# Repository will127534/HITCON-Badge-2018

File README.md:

# HITCON-Badge-2018
HITCON Badge 2018 files

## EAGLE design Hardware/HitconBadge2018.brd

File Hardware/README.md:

#Hitcon Badge 2018 硬體架構
---

幾個重要的Chip分別如下:
Main System on Chip: MT7697[官方網頁](https://labs.mediatek.com/zh-tw/chipset/MT7697)  
NFC Controller: PN532  
Display: Waveshare 2.13" [官方網頁](https://www.waveshare.com/wiki/2.13inch_e-Paper_HAT)  
Secure Element: SLE97

MT7697的周邊是基於LinkIt 7697[(官方網頁)](https://docs.labs.mediatek.com/resource/mt7687-mt7697/en/get-started-linkit-7697-hdk) 開發版所做的二次開發，所以使用上如同LinkIt 7697

接下來分幾個子系統來說明  

### e-Paper:  

Waveshare 2.13" e-Paper 解析度為250x122的黑白雙色的電子紙且支援區域更新
和MT7697的接線圖如下表:

| E-Paper pin | MT7697 pin | Arduino |
| -------- | -------- | -------- |
| Busy     | GPIO34     | 4     |
| RST     | GPIO33     | 5     |
| D/C     | GPIO36     | 7     |
| /CS     | GPIO32     | 10     |
| SCK     | GPIO31     | 13     |
| MOSI     | GPIO29     | 11     |
  
電子紙的Graphics Library使用的是Adafruit GFX [(Link)](https://learn.adafruit.com/adafruit-gfx-graphics-library/overview)
Adafruit GFX提供了幾個畫圖的操作API，不過要注意的是只有黑白兩色  
而底層的電子紙控制則是用GxEPD Library[(Link)](https://github.com/ZinggJM/GxEPD)
另外就是由於電子紙的全域更新速度較慢，這個型號另外提供了一個區域更新的方法，也就是只更新部分區域的畫面  
但是要注意的是區域更新會有殘影留在螢幕上，所以幾次的區域更新之後需要一次全域更新去清除殘影。全域更新大約需要6s，而區域更新只需要<0.5s  

### NFC:
也是用Adafruit的Library [(Link)](https://github.com/adafruit/Adafruit-PN532)
和MT7697的接線圖如下表:

| PN532 | MT7697 pin | Arduino |
| -------- | -------- | -------- |
| I2C     | I2C     | I2C     |
| RST     | GPIO60     | 17     |
| INT     | GPIO0     | 2     |

### Secure Element:  
待Update
和MT7697的接線圖如下表:

| SLE97 | MT7697 pin | Arduino |
| -------- | -------- | -------- |
| SPI     | SPI     | SPI     |
| CS     | GPIO39     | 3     |

### Button Array:  
由於MT7697 IO不夠用了，所以矩陣鍵盤使用的是類比的方式，
藉由按鈕按下後所產生的不同組合的電阻產生的電壓去判定是哪一個按鈕被按下。
由於MT7697內建的ADC有4096階，使用上問題不大。
按鈕 A,B,C,0-9,DEL,ENTER都在Array裡面。 

| Button Array | MT7697 pin | Arduino |
| -------- | -------- | -------- |
| Analog Voltage     | GPIO58     | A1     |
### Special Buttons:  
由於MT7697設計上需要一個Bootstarp pin去切換Bootloader or User code，
所以GPIO37的Button在剛開機時作為強制切進Bootloader的方法，開機後就是一個普通的按鈕
另外一個按鈕則是RST按下之後MT7697會強制Reset。

| Function Name | MT7697 pin | Arduino |
| -------- | -------- | -------- |
| RST     | RST     | N/A     |
| Button D     | GPIO37     | 6     |

切進Bootloader的方式為:按下Reset和Button D，放開Reset之後放開Button D即可。
另外要注意的是，Button D按下之後 GPIO37是高電位，放開則低電位，所以邏輯上是按下為1，放開為0。

### LEDs:  

|  Name | Function |
| -------- | -------- |
| USR     | GPIO57,Arduino pin A0     |
| RX     | USB to UART RX訊號燈     |
| TX     | USB to UART TX訊號燈     |
| Power    | 電源指示燈     |

USR Led是一個簡單的LED接在MT7697上，IO拉高點亮，拉低則關閉。
另外Power LED旁邊有一個焊接的Jumper，可以把這個Jumper斷開以省電。

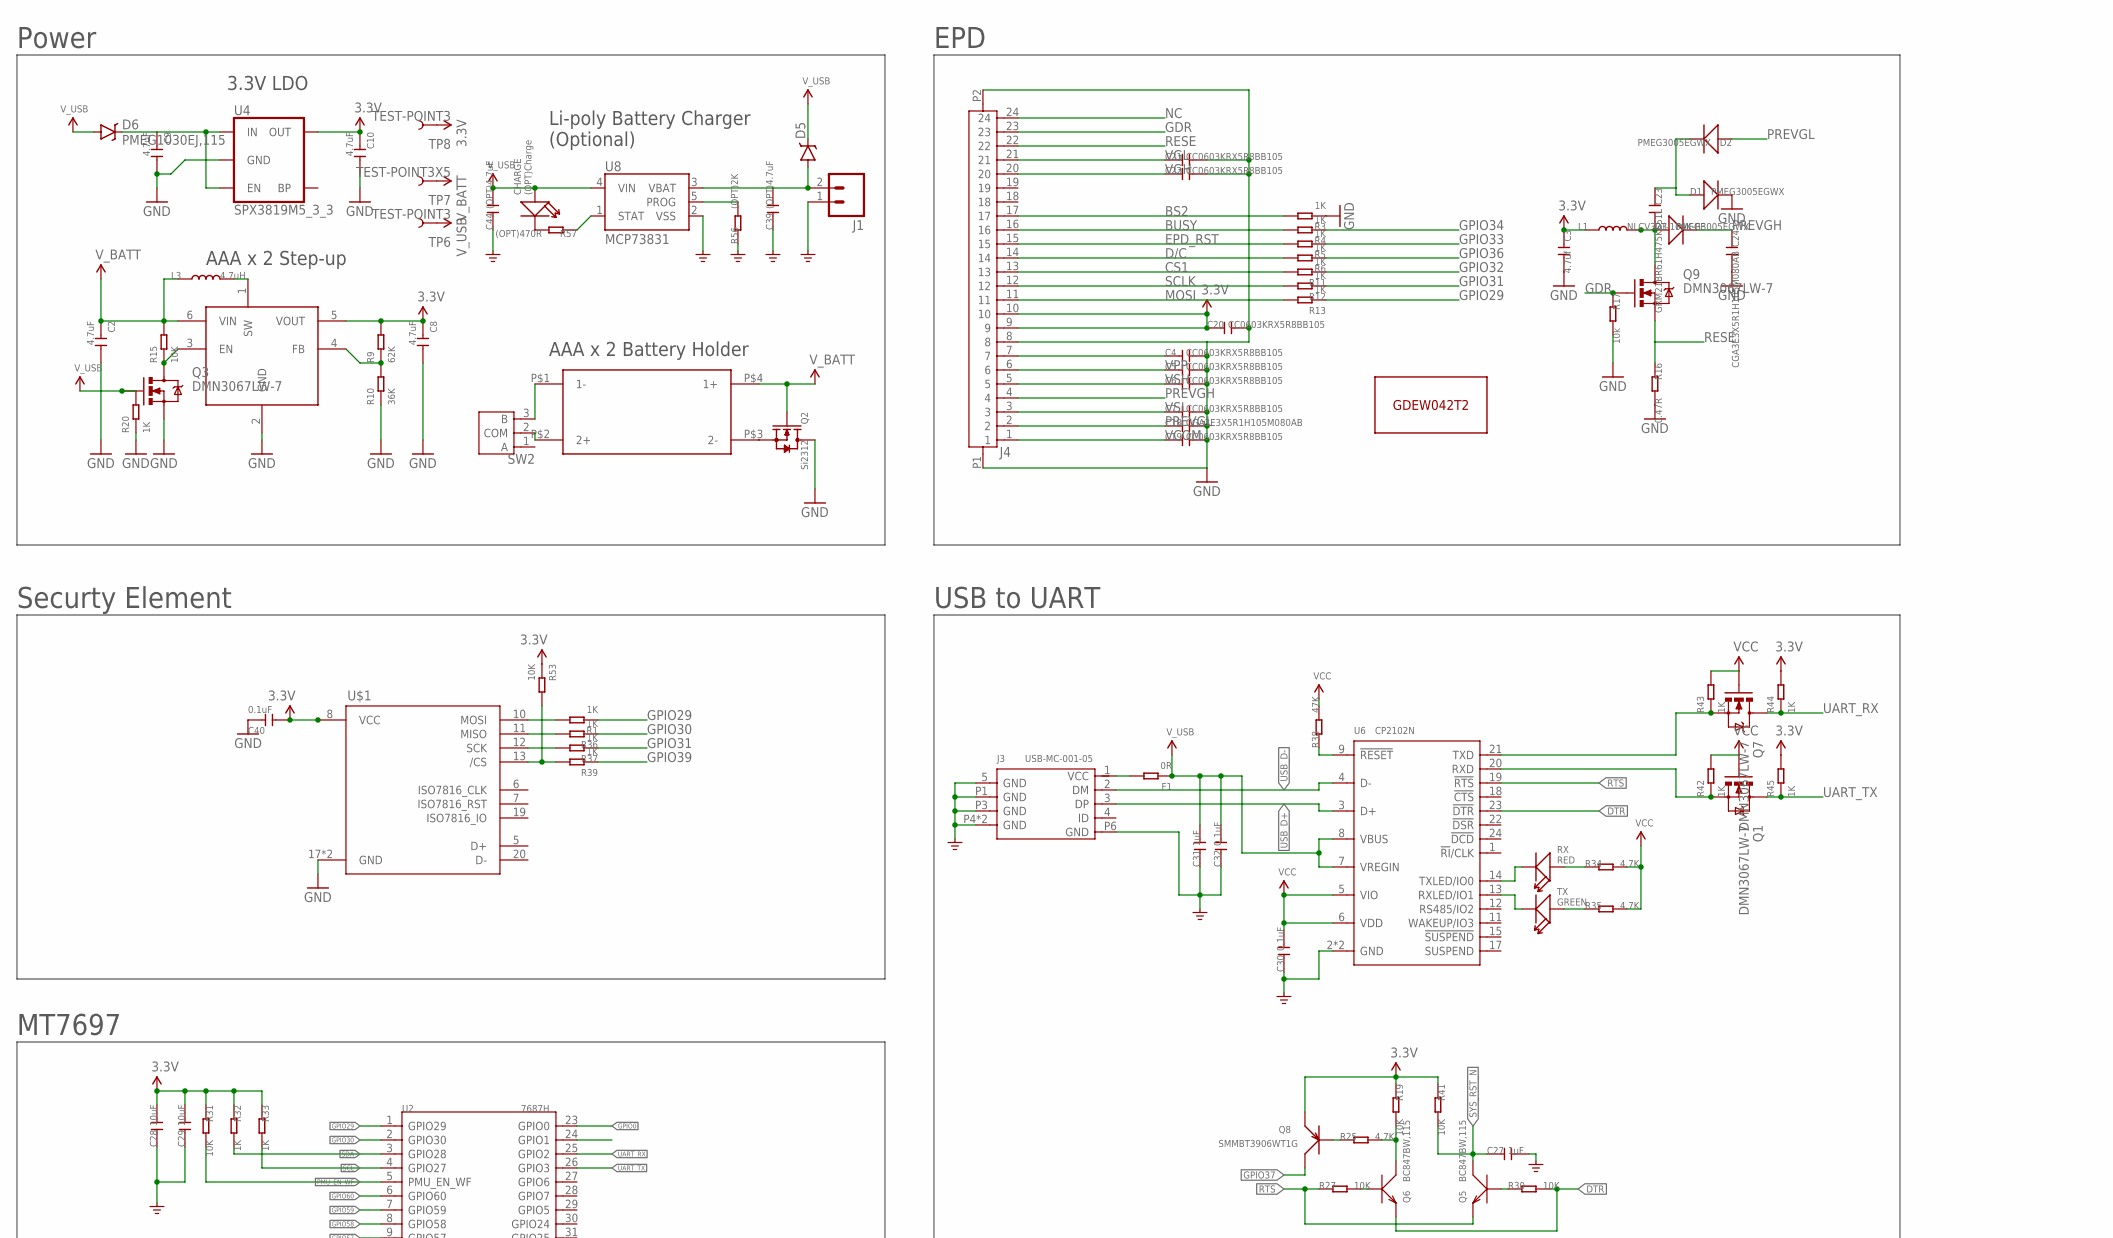
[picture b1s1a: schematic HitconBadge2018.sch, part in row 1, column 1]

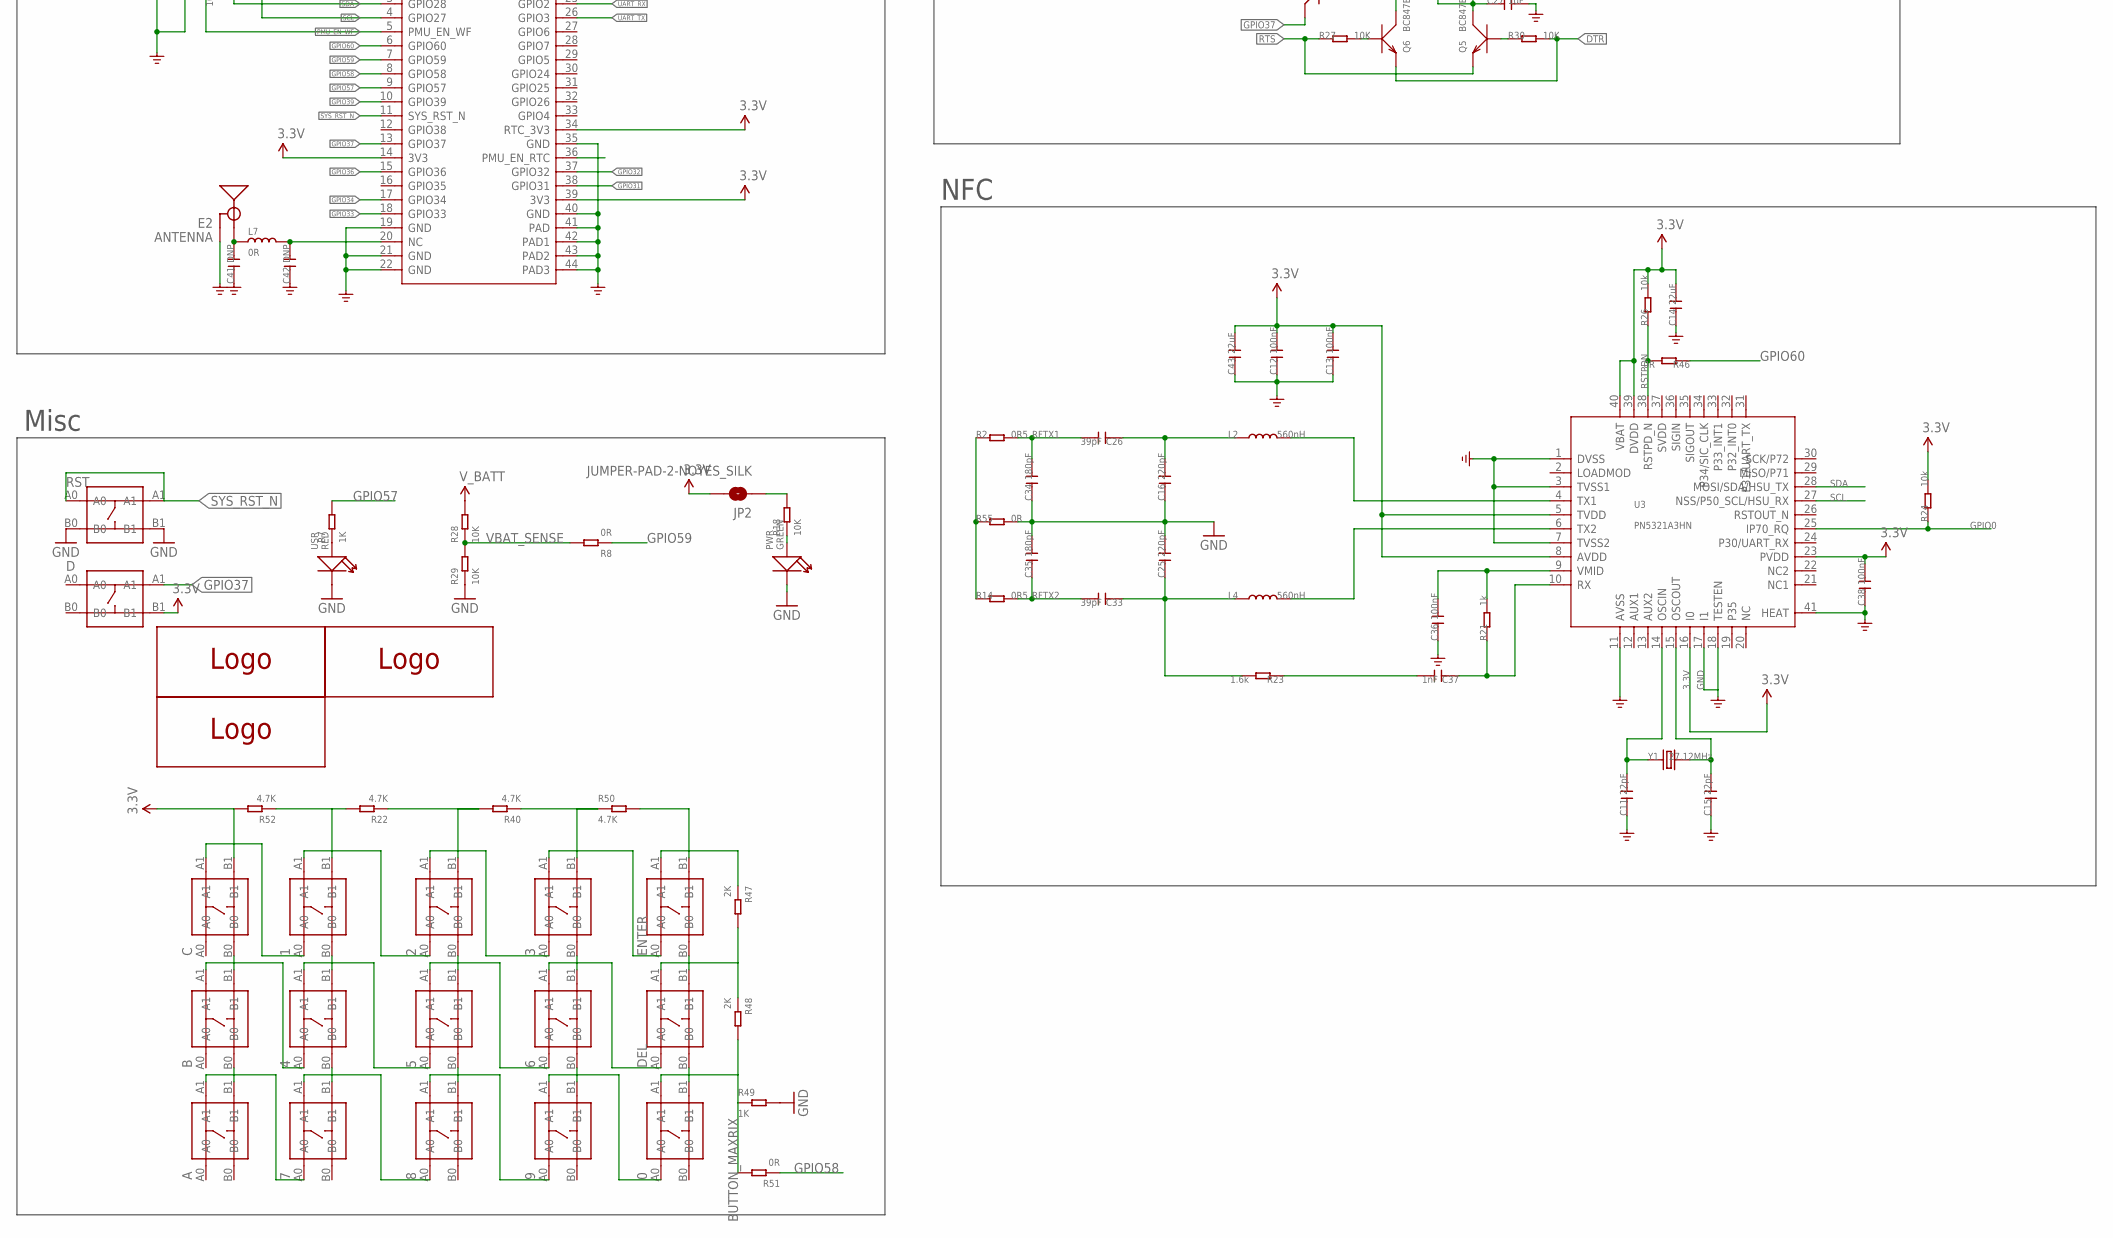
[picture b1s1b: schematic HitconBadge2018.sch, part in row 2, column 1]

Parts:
0, 1, 2, 3, 4, 5, 6, 7, 8, 9: BUTTON-4P-3.3X3.3; 4P-SMD-3.4X3.4X1.3H
A: BUTTON-4P-3.3X3.3; 4P-SMD-3.4X3.4X1.3H
B: BUTTON-4P-3.3X3.3; 4P-SMD-3.4X3.4X1.3H
C: BUTTON-4P-3.3X3.3; 4P-SMD-3.4X3.4X1.3H
C2, C8, C9, C10: 4.7uF; C0603@1
C3: 4.7uf; C0603
C4, C5, C6, C7, C19, C20, C21, C22: CC0603KRX5R8BB105; C0603
C11, C15: 22pF; C0402
C12, C13, C36, C38: 100nF; C0402
C14, C43: 22uF; C0603
C16, C25: 220pF; C0402
C18, C24: CGA3E3X5R1H105M080AB; C0603
C23: GRM21BR61H475KE51L; C0805
C26, C33: 39pF; C0402
C27, C31: 1uF; C0402
C28, C29: 10uF; C0603
C30, C32: 0.1uF; C0402
C34, C35: 180pF; C0402
C37: 1nF; C0402
C39, C44: (OPT)4.7uF; C0603
C40: 0.1uF; C0402@1
C41, C42: DNP; C0402
CHARGE: (OPT)Charge; LED-0603
D: BUTTON-4P-3.3X3.3; 4P-SMD-3.4X3.4X1.3H
D1, D2, D3: PMEG3005EGWX; SOD123
D5: (OPT)PMEG1030EJ,115; SOD-323
D6: PMEG1030EJ,115; SOD-323
DEL: BUTTON-4P-3.3X3.3; 4P-SMD-3.4X3.4X1.3H
E2: ANTENNA; 2450AT18D0100E
ENTER: BUTTON-4P-3.3X3.3; 4P-SMD-3.4X3.4X1.3H
F1: 0R; R0603
J1: M02-JST-2MM-SMT; JST-2-SMD
J3: USB-MC-001-05; MICRO-USB5+5P-SMD-0.65-7.2X5.06MM
J4: FPC-CONNECTOR-24P-0.5'ST-FPC-052024-B'; 24P-0.5
JP2: JUMPER-PAD-2-NOYES_SILK; PAD-JUMPER-2-NO_YES_SILK
L1: NLCV32T-100K-PF; 1813@1
L2, L4: 560nH; L0603@1
L3: 4.7uH; 1616BZ@1
L7: 0R; L0402
PWR: GREEN; LED-0603
Q1, Q3, Q7, Q9: DMN3067LW-7; SOT323
Q2: Si2312; SOT23
Q5, Q6: BC847BW,115; SOT-323
Q8: SMMBT3906WT1G; SOT-323
R1, R3, R4, R5, R6, R7, R11, R12, R13, R20, R32, R33, R36, R37, R39, R42, R43, R44, R45, R49: 1K; R0402
R2, R14: 0R5; R0402
R8, R46, R51, R55: 0R; R0402
R9: 62K; R0402
R10: 36K; R0402
R15, R18, R19, R27, R28, R29, R30, R31, R41, R53: 10K; R0402
R16: 0.47R; R0402
R17, R24, R26: 10k; R0402
R21: 1k; R0402
R22, R25, R34, R35, R40, R50, R52: 4.7K; R0402
R23: 1.6k; R0402
R38: 47K; R0402
R47, R48: 2K; R0402
R56: (OPT)2K; R0402
R57: (OPT)470R; R0402
RST: BUTTON-4P-3.3X3.3; 4P-SMD-3.4X3.4X1.3H
RX: RED; LED-0603
SW2: SWITCH-2H-3P'--'; 3P-2CH-3.54X8.5
TP6, TP8: TEST-POINT3; PAD.03X.03
TP7: TEST-POINT3X5; PAD.03X.05
TX: GREEN; LED-0603
U1: MCP1640; SOT23-6
U2: 7687H; MODULE44P-1.6-18X18X1.3MM
U3: PN5321A3HN; HVQFN40
U4: SPX3819M5_3_3; SOT23-5
U6: CP2102N; QFN24G-0.5-4X4MM
U8: MCP73831; SOT23-5
U$1: SLE97; QFN-32
U$2: HITCON_LOGOHITCON; HITCON_LOGO
U$3: HITCON_LOGOMEDIATEK; MEDIATEK
U$4: AAAX2
U$5: 213
U$6: HITCON_LOGOIKV; IKV
USR: RED; LED-0603
Y1: 27.12MHz; 4P-SMD-3.2X2.5

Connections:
3.3V: C.B1, C3.1, C8.1, C10.1, C12.2, C13.2, C14.2, C20.1, C28.2, C29.2, C38.2, C40.2, C43.2, D.B1, J4.9, J4.10, JP2.2, L1.1, Q8.2 (E), R9.2, R19.1, R24.2, R26.2, R31.1, R32.1, R33.1, R41.1, R44.2, R45.2, R52.2, R53.1, TP8.P$1, U1.5 (VOUT), U2.14 (3V3), U2.34 (RTC_3V3), U2.39 (3V3), U3.5 (TVDD), U3.8 (AVDD), U3.16 (I0), U3.23 (PVDD), U3.39 (DVDD), U3.40 (VBAT), U4.5 (OUT), U$1.8 (VCC)
BS2: J4.17, R3.2
BUSY: J4.16, R4.2
BUTTON_MAXRIX: 0.A1, R48.2, R49.1, R51.2
CS1: J4.13, R11.2
D/C: J4.14, R6.2
DTR: Q6.2 (E), R30.2, U6.23 (!DTR!)
EPD_RST: J4.15, R5.2
GDR: J4.23, Q9.1 (G), R17.1
GND: C2.2, C3.2, C4.2, C5.2, C6.2, C7.2, C8.2, C9.2, C10.2, C11.1, C12.1, C13.1, C14.1, C15.1, C16.1, C18.2, C19.2, C20.2, C21.2, C22.2, C24.2, C25.2, C27.2, C28.1, C29.1, C30.1, C31.1, C32.1, C34.1, C35.2, C36.1, C38.1, C39.1, C40.1, C41.1, C42.1, C43.1, C44.1, D1.-, E2.GND@1 (GND), E2.GND@2 (GND), E2.GND@3 (GND), J1.1 (2), J3.5 (GND), J3.P1 (GND), J3.P3 (GND), J3.P4 (GND), J3.P5 (GND), J3.P6 (GND), J4.8, J4.P1, J4.P2, PWR.-, Q2.3 (D), Q3.2 (S), R3.1, R10.1, R16.2, R17.2, R20.1, R29.1, R49.2, R55.2, R56.1, RST.B0, RST.B1, U1.2 (GND), U2.19 (GND), U2.21 (GND), U2.22 (GND), U2.35 (GND), U2.40 (GND), U2.41 (PAD), U2.42 (PAD1), U2.43 (PAD2), U2.44 (PAD3), U3.1 (DVSS), U3.3 (TVSS1), U3.7 (TVSS2), U3.11 (AVSS), U3.17 (I1), U3.18 (TESTEN), U3.41 (HEAT), U4.2 (GND), U6.2 (GND), U6.PAD (GND), U8.2 (VSS), U$1.17 (GND), U$1.EP (GND), USR.-
GPIO0: R24.1, U2.23 (GPIO0), U3.25 (IP70_RQ)
GPIO29: R1.1, R13.1, U2.1 (GPIO29)
GPIO30: R36.1, U2.2 (GPIO30)
GPIO31: R12.1, R37.1, U2.38 (GPIO31)
GPIO32: R11.1, U2.37 (GPIO32)
GPIO33: R5.1, U2.18 (GPIO33)
GPIO34: R4.1, U2.17 (GPIO34)
GPIO36: R6.1, U2.15 (GPIO36)
GPIO37: D.A1, Q8.3 (C), U2.13 (GPIO37)
GPIO39: R39.1, U2.10 (GPIO39)
GPIO57: R7.2, U2.9 (GPIO57)
GPIO58: R51.1, U2.8 (GPIO58)
GPIO59: R8.1, U2.7 (GPIO59)
GPIO60: R46.1, U2.6 (GPIO60)
MOSI: J4.11, R13.2
unnamed: C11.2, U3.14 (OSCIN), Y1.2 (1)
unnamed: L3.2, U1.1 (SW)
unnamed: C23.1, D1.+, D2.-
unnamed: SW2.3 (B), U$4.P$1 (1-)
unnamed: R7.1, USR.+
unnamed: R9.1, R10.2, U1.4 (FB)
unnamed: Q3.3 (D), R15.1, U1.3 (EN)
unnamed: C15.2, U3.15 (OSCOUT), Y1.4 (2)
unnamed: L4.2, U3.6 (TX2)
unnamed: L2.2, U3.4 (TX1)
unnamed: C4.1, J4.7
unnamed: C16.2, C26.1, L2.1
unnamed: C23.2, D3.+, L1.2, Q9.3 (D)
unnamed: C25.1, C33.1, L4.1, R23.2
unnamed: C36.2, R21.2, U3.9 (VMID)
unnamed: C37.1, R21.1, U3.10 (RX)
unnamed: C37.2, R23.1
unnamed: 4.B0, 7.B1
unnamed: C41.2, E2.FEED (SIGNAL), L7.1
unnamed: 1.B0, 4.B1
unnamed: SW2.2 (COM), U$4.P$2 (2+)
unnamed: C9.1, D6.C, U4.1 (IN), U4.3 (EN)
unnamed: R56.2, U8.5 (PROG)
unnamed: 5.B0, 8.B1
unnamed: C42.2, L7.2, U2.20 (NC)
unnamed: R1.2, U$1.10 (MOSI)
unnamed: R36.2, U$1.11 (MISO)
unnamed: R37.2, U$1.12 (SCK)
unnamed: R39.2, R53.2, U$1.13 (/CS)
unnamed: 2.B0, 5.B1
unnamed: 2.B1, R22.1, R40.2
unnamed: 6.B0, 9.B1
unnamed: 3.B0, 6.B1
unnamed: 3.B1, R40.1, R50.1
unnamed: 0.B1, DEL.B0
unnamed: DEL.B1, ENTER.B0
unnamed: ENTER.B1, R50.2
unnamed: PWR.+, R18.1
unnamed: JP2.1, R18.2
unnamed: F1.2, J3.1 (VCC)
unnamed: Q5.1 (B), R30.1
unnamed: Q6.1 (B), R27.2
unnamed: Q6.3 (C), R19.2, R25.2
unnamed: Q8.1 (B), R25.1
unnamed: R35.1, TX.+
unnamed: R34.1, RX.+
unnamed: TX.-, U6.13 (RXLED/IO1)
unnamed: RX.-, U6.14 (TXLED/IO0)
unnamed: R38.1, U6.9 (!RESET!)
unnamed: Q1.2 (S), R42.1, U6.20 (RXD)
unnamed: Q7.2 (S), R43.1, U6.21 (TXD)
unnamed: 6.A1, DEL.A0
unnamed: 3.A1, ENTER.A0
unnamed: 7.A1, 8.A0
unnamed: 8.A1, 9.A0
unnamed: 0.A0, 9.A1
unnamed: 4.A1, 5.A0
unnamed: 5.A1, 6.A0
unnamed: DEL.A1, R47.2, R48.1
unnamed: 1.A1, 2.A0
unnamed: 2.A1, 3.A0
unnamed: ENTER.A1, R47.1
unnamed: R2.1, R14.1, R55.1
unnamed: Q2.2 (S), U$4.P$3 (2-)
unnamed: R57.1, U8.1 (STAT)
unnamed: CHARGE.-, R57.2
unnamed: 1.B1, R22.2, R52.1
unnamed: C39.2, D5.A, J1.2 (1), U8.3 (VBAT)
unnamed: B.B1, C.B0
unnamed: A.B1, B.B0
unnamed: 7.A0, A.A1
unnamed: 4.A0, B.A1
unnamed: 1.A0, C.A1
NC: J4.24
PMU_EN_RTC: U2.36 (PMU_EN_RTC)
PMU_EN_WF: R31.2, U2.5 (PMU_EN_WF)
PREVGH: C24.1, D3.-, J4.4
PREVGL: C18.1, D2.+, J4.2
RESE: J4.22, Q9.2 (S), R16.1
RFTX1: C26.2, C34.2, R2.2
RFTX2: C33.2, C35.1, R14.2
RSTPDN: R26.1, R46.2, U3.38 (RSTPD_N)
RTS: Q5.2 (E), R27.1, U6.19 (!RTS!)
SCL: R33.2, U2.4 (GPIO27), U3.27 (NSS/P50_SCL/HSU_RX)
SCLK: J4.12, R12.2
SDA: R32.2, U2.3 (GPIO28), U3.28 (MOSI/SDA/HSU_TX)
SYS_RST_N: C27.1, Q5.3 (C), R41.2, RST.A0, RST.A1, U2.11 (SYS_RST_N)
UART_RX: Q7.3 (D), R44.1, U2.25 (GPIO2)
UART_TX: Q1.3 (D), R45.1, U2.26 (GPIO3)
USB_D+: J3.3 (DP), U6.3 (D+)
USB_D-: J3.2 (DM), U6.4 (D-)
VBAT_SENSE: R8.2, R28.1, R29.2
VCC: C30.2, Q1.1 (G), Q7.1 (G), R34.2, R35.2, R38.2, R42.2, R43.2, U6.5 (VIO), U6.6 (VDD)
VCOM: C19.1, J4.1
VGH: C22.1, J4.20
VGL: C21.1, J4.21
VPP: C5.1, J4.6
VSH: C6.1, J4.5
VSL: C7.1, J4.3
V_BATT: C2.1, L3.1, Q2.1 (G), R15.2, R28.2, TP7.P$1, U1.6 (VIN), U$4.P$4 (1+)
V_USB: C31.2, C32.2, C44.2, CHARGE.+, D5.C, D6.A, F1.1, Q3.1 (G), R20.2, TP6.P$1, U6.7 (VREGIN), U6.8 (VBUS), U8.4 (VIN)

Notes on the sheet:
Misc
Power
EPD
MT7697
USB to UART
NFC
Securty Element
3.3V LDO
Li-poly Battery Charger (Optional)
AAA x 2 Step-up
AAA x 2 Battery Holder

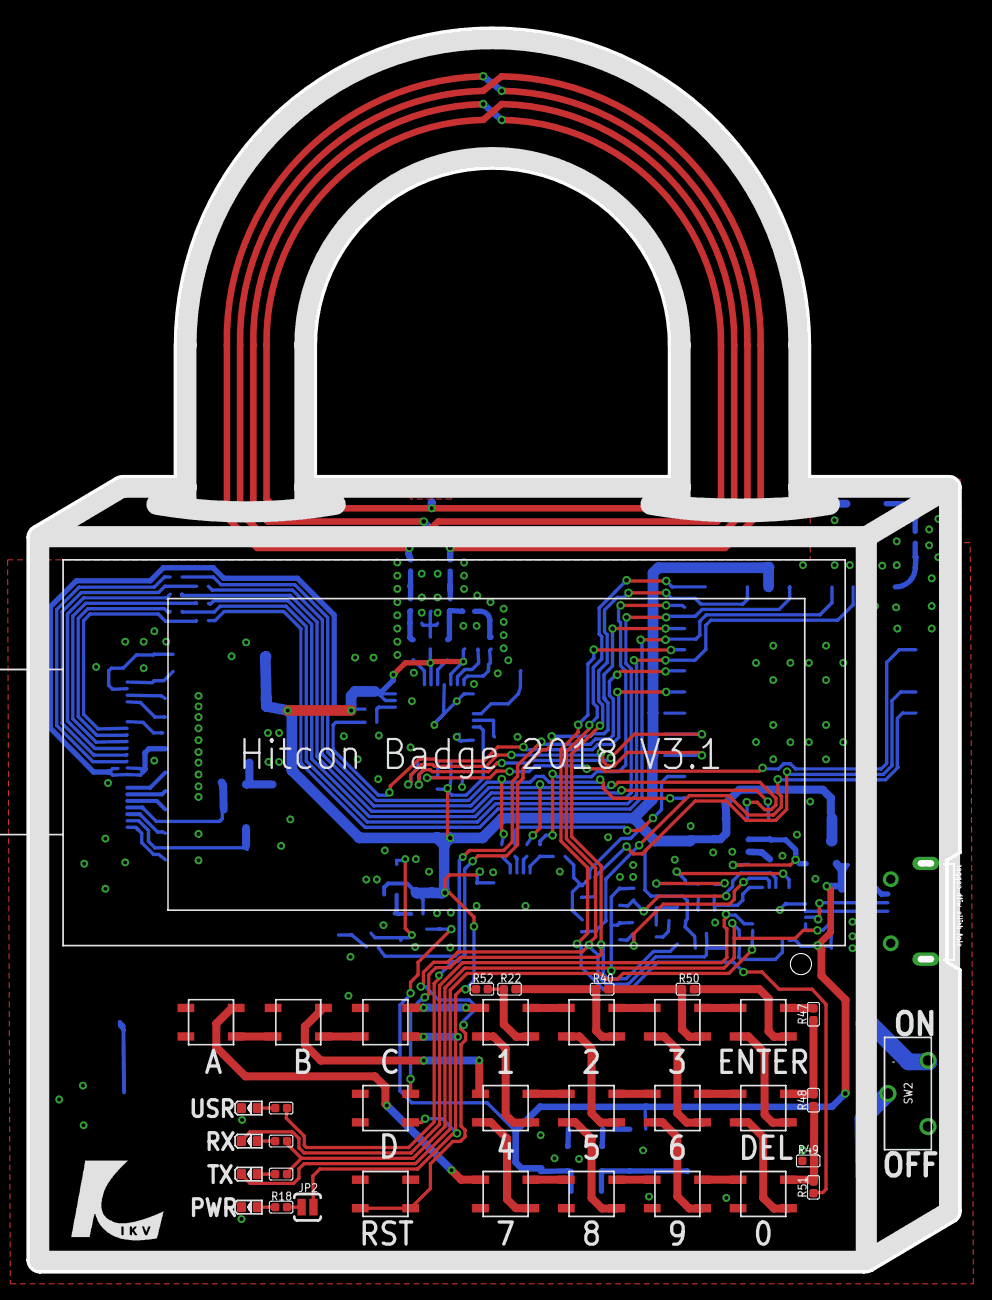
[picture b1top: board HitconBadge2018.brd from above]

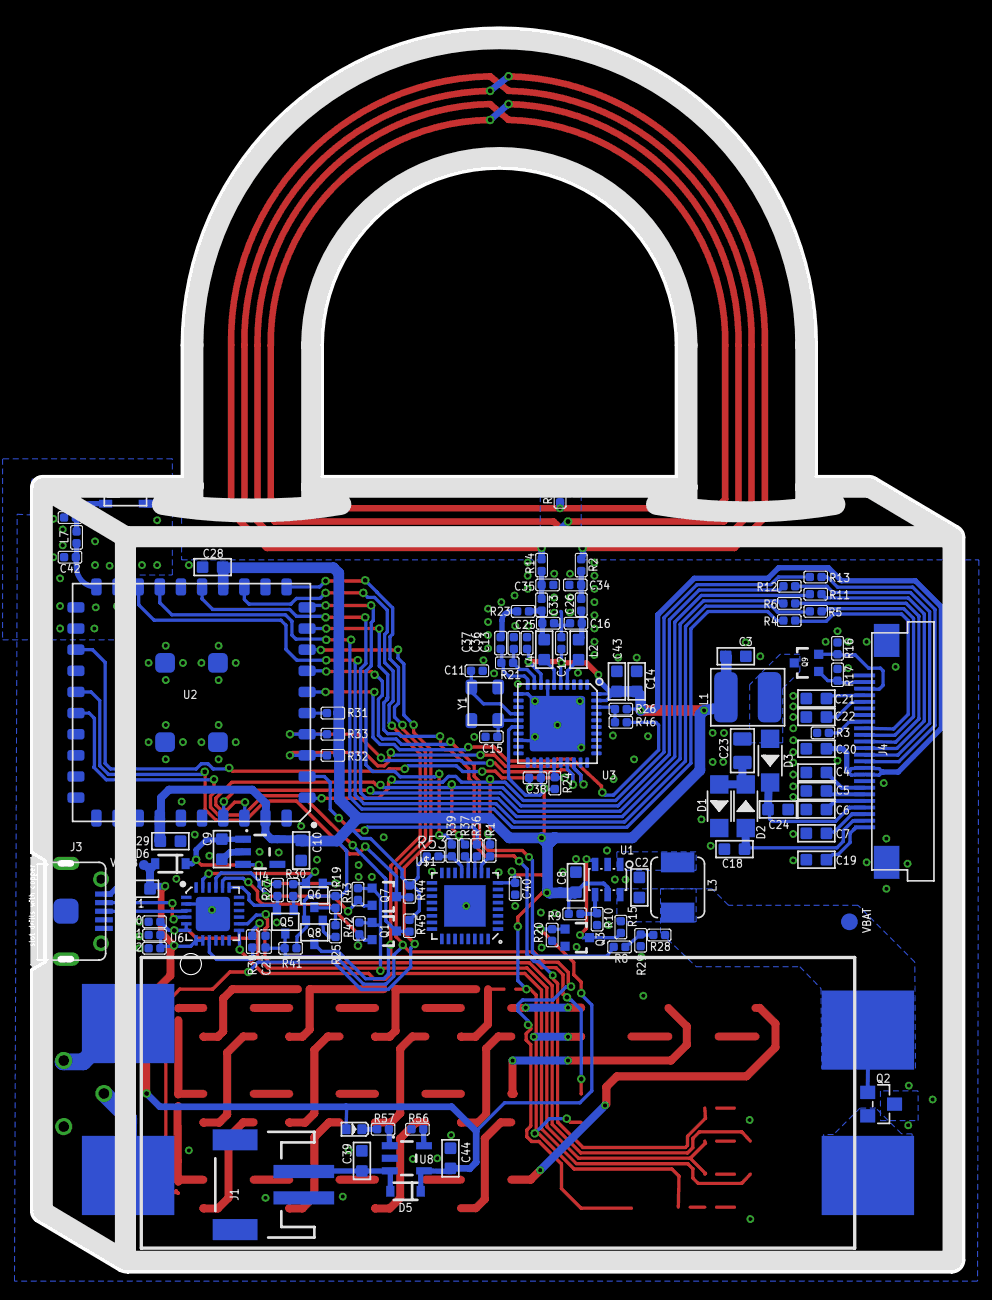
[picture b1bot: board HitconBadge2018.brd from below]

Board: 2 copper layers, 70.6 x 94.2 mm, 161 parts (123 on the bottom side), 124 nets.

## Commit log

2018-05-10 init V0.01
2018-05-10 add python BLE example code
2018-05-11 Adding ERC20 support 0.1 and fix RLP encoder bug
2018-05-24 adding Adafruit GFX library
2018-05-24 move GFX to library folder
2018-06-09 Update BLE adding Rand UUID and new interface
2018-06-11 Change BLE and adding Balance update support
2018-06-18 adding Upload tools and update main program and BLE with bin file
2018-06-18 update BLE example
2018-06-19 adding AES enc
2018-06-20 adding Arduino Packages
2018-06-20 update Arduino Packages json
2018-06-20 update bin file
2018-06-21 adding QR spec
2018-06-22 adding Battery Service
2018-07-04 fix nonce 15 error
2018-07-04 fix Txn BLE
2018-07-09 update UI and BLE adding Transaction Page
2018-07-09 adding binaty
2018-07-26 Ver 1.0
2018-07-26 Adding Hardware Readme
2018-07-28 Add powerpoint
2018-08-07 Adding some info about software
2018-08-20 Changing NFC Library to emulate NFC Tag
2018-08-20 Change NFC library description
    Changed to Modified Seeedstudio PN532 library for NFC Card emulation.
2018-08-23 V1.1 package, added example for E-ink and SE
2018-08-27 Update SE library
2018-09-18 Update SE firmware
    Update SE firmware for auto clear data when Pin code failed 10 times,
    which SE will go back to NO HOST mode.
2018-09-18 Updated new SE firmare. If transaction failed 10 times, SE will clear data and go back to NOHOST state.
2019-02-01 Create MyoBridge

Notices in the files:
parts and their libraries:
SparkFun-Passives: Licensing: Creative Commons ShareAlike 4.0 International - https://creativecommons.org/licenses/by-sa/4.0
